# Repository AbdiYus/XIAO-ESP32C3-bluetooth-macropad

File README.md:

# XIAO-ESP32C3 bluetooth Macropad (C3_Pad) 
A custom Macropad using a Xiao esp32c3 micorcontroller. 

This projects includes: 
- Arduino sketch
- PCB design
- Bill of material 
- 3d print case 

## Arduino sketch 
The project requires these libraries to compile: 
- [Encoder by Paul Stoffregen](https://github.com/PaulStoffregen/Encoder)
- [u8g2 by olikarus](https://github.com/olikraus/u8g2)
- [ESP32-BLE-Combo by Georgegipa](https://github.com/Georgegipa/ESP32-BLE-Combo)

## PCB design
I'm new to PCB design and __highly recommend__ you to check it out before using the design. 

### Schematic 

__N.B!__ 
The xiao esp32c3 symbol doesn't include the battery connectors. So, I've manualy connected them on the PCB editor

### pcb

### 3d model

# Bill of material (BOM)
| component             | website | 
| --------              | ------- |
| SSD1306 OLED          | [link](https://www.amazon.com/HiLetgo-Adafruit-Beaglebones-Raspberry-Optional/dp/B06XRBYJR8?th=1)    |
| KY-040 encoder        | [link](https://www.amazon.com/JTAREA-KY-040-Encoder-Encoders-Modules/dp/B0D2TW63G1/ref=sr_1_1_sspa?)   |
| TP4056 charger        | [link](https://www.amazon.com/HiLetgo-Lithium-Charging-Protection-Functions/dp/B07PKND8KG/ref=sr_1_1_sspa?)    |
| Cherry MX silent red  | [link](https://www.amazon.com/Cherry-MX-RGB-Mechanical-Keyboard/dp/B0CBS4QYXS/ref=sr_1_1?)    |
| Xiao ESP32c3          | [link](https://www.seeedstudio.com/Seeed-XIAO-ESP32C3-p-5431.html)     |

# 3d print case 
__Not finished__

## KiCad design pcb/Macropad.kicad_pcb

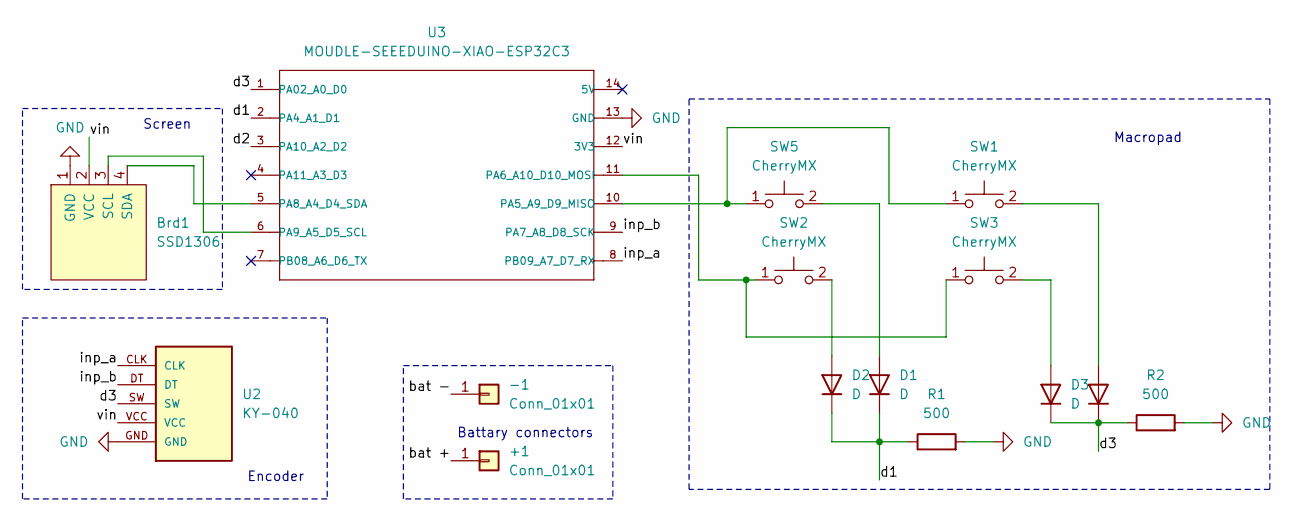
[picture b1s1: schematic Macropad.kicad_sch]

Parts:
+1: Conn_01x01; TestPoint_Pad_4.0x4.0mm
-1: Conn_01x01; TestPoint_Pad_4.0x4.0mm
Brd1: SSD1306; 128x64OLED
D1, D2, D3, D4: D; D_0805_2012Metric
R1, R2: 500; R_0805_2012Metric
SW1, SW2, SW3, SW5: CherryMX; CherryMX_1.00u
U2: KY-040; KY-040-PORT
U3: MOUDLE-SEEEDUINO-XIAO-ESP32C3; MCU_Seeed_ESP32C3

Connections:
/bat +: +1.1, U3.16
/bat -: -1.1, U3.17
/d1: D1.1 (K), D2.1 (K), R1.1, U3.2 (PA4_A1_D1)
/d2: U3.3 (PA10_A2_D2)
/d3: D3.1 (K), D4.1 (K), R2.1, U2.SW, U3.1 (PA02_A0_D0)
/inp_a: U2.CLK, U3.8 (PB09_A7_D7_RX)
/inp_b: U2.DT, U3.9 (PA7_A8_D8_SCK)
/vin: Brd1.2 (VCC), U2.VCC, U3.12 (3V3)
GND: Brd1.1 (GND), R1.2, R2.2, U2.GND, U3.13 (GND)
unnamed: Brd1.3 (SCL), U3.6 (PA9_A5_D5_SCL)
unnamed: Brd1.4 (SDA), U3.5 (PA8_A4_D4_SDA)
unnamed: D1.2 (A), SW5.2
unnamed: D2.2 (A), SW2.2
unnamed: D3.2 (A), SW3.2
unnamed: D4.2 (A), SW1.2
unnamed: SW1.1, SW5.1, U3.10 (PA5_A9_D9_MISO)
unnamed: SW2.1, SW3.1, U3.11 (PA6_A10_D10_MOSI)

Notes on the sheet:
Encoder
Battary connectors
Macropad
Screen

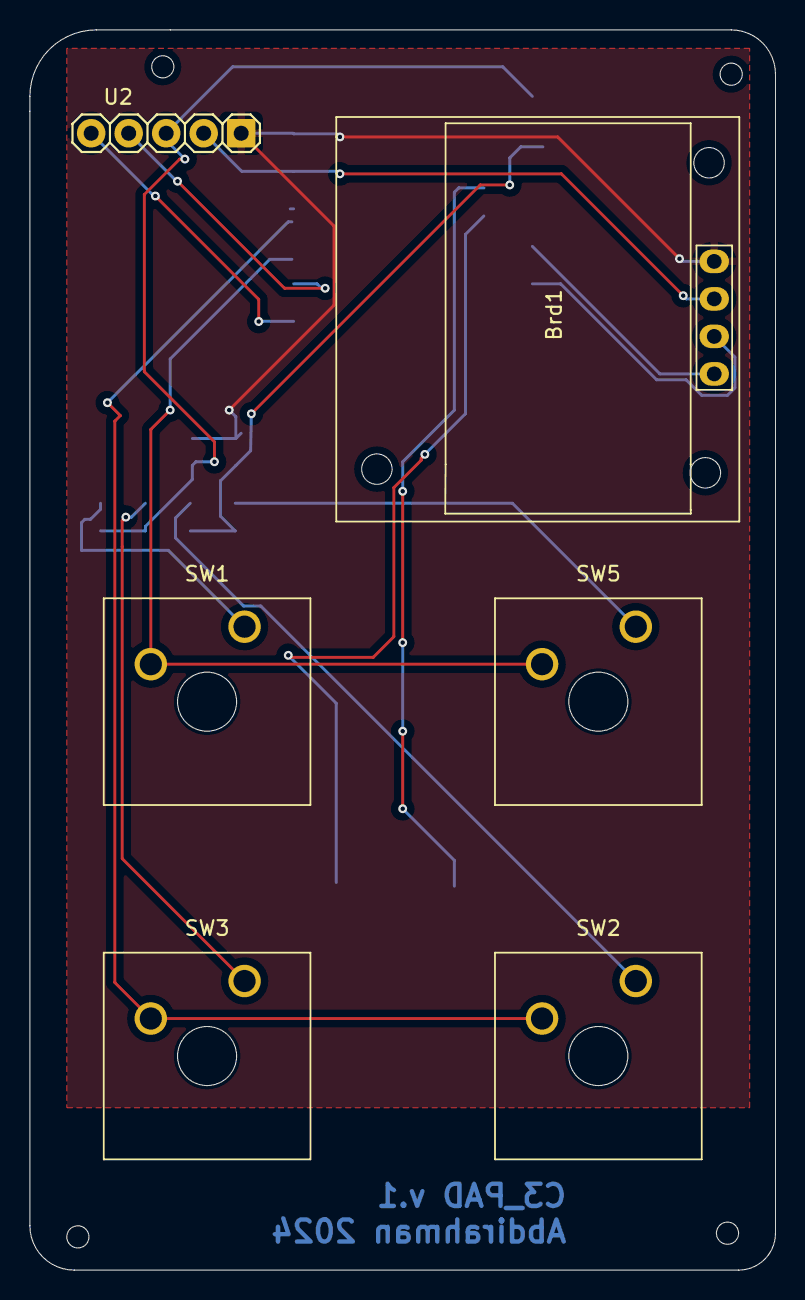
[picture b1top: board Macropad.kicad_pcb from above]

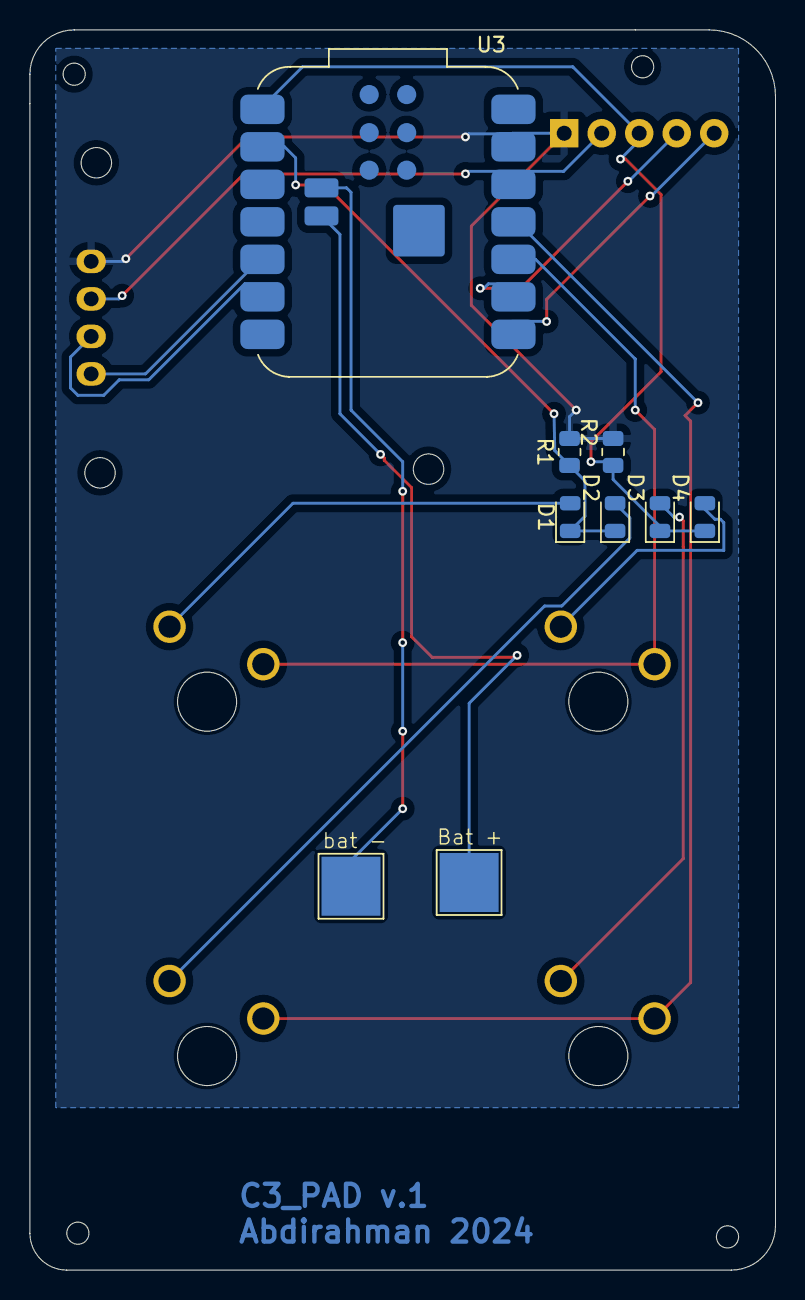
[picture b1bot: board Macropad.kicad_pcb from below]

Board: 2 copper layers, 50.5 x 84.0 mm, 15 parts (9 on the bottom side), 16 nets.

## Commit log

2024-01-06 adding code directory
2024-01-07 progress
2024-01-07 testing code
2024-01-07 fixing #
2024-01-07 test
2024-01-07 2x2 matrix
2024-01-07 commenting
2024-01-07 readme
2024-01-07 text
2024-01-07 added text
2024-01-07 kicad
2024-01-07 inital pcb
2024-01-09 added keyboard libraries
2024-08-04 added encoder + setup to screen
2024-08-04 pcb v.01
2024-08-04 change readme
2024-08-11 changed to ble keyboard libraries
2024-08-13 added ble libraries + screen
2024-08-14 beta
2024-08-15 code v.1 done
2024-09-09 code
